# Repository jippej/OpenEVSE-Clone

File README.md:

# OpenEVSE-Clone

This is an hardware design which is based on OpenEVSE, compatible with the OpenEVSE firmware, and suited to my needs.
Key changes in respect to the original OpenEVSE boards (version 5.5):
- Removed DC relais control (I use a AC controlled relais)
- GFCI detection removed (I use an external ELCB)
- Removed AC/DC converter (I use an external DIN rail mounted 12VDC supply)
- form factor adjusted to be fitted in a standard DIN rail housing
- Added H-Bridge driver for "cable lock" mechanism
- Added mounting for ESP32 Gateway

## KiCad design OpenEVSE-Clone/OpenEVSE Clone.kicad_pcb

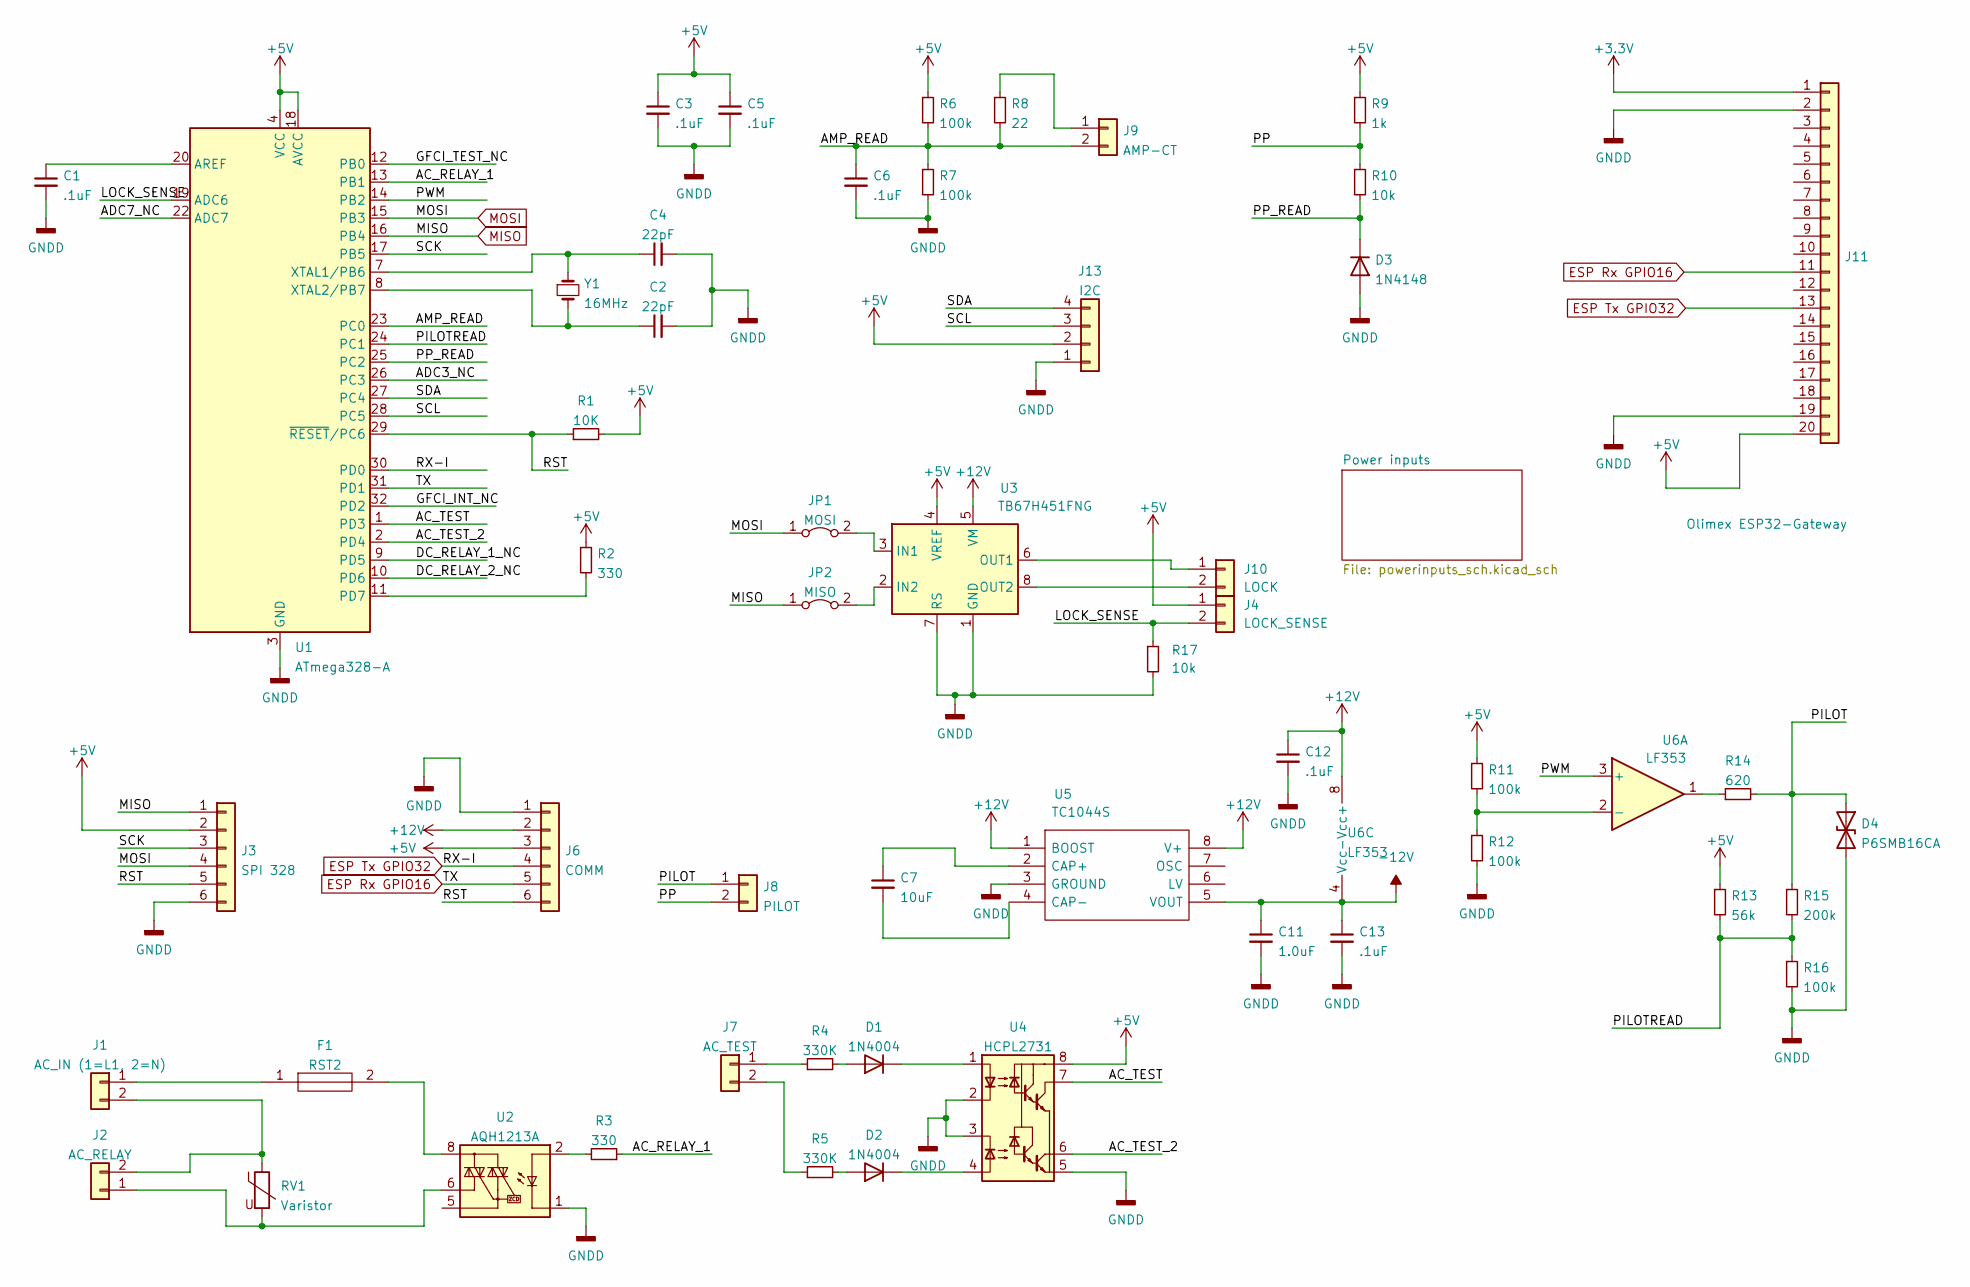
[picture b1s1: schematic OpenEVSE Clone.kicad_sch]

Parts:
C1, C3, C5, C6, C12, C13: .1uF; C_0805_2012Metric_Pad1.18x1.45mm_HandSolder
C2, C4: 22pF; C_0805_2012Metric_Pad1.18x1.45mm_HandSolder
C7: 10uF; C_0805_2012Metric_Pad1.18x1.45mm_HandSolder
C11: 1.0uF; C_0805_2012Metric_Pad1.18x1.45mm_HandSolder
D1, D2: 1N4004; D_SMA
D3: 1N4148; D_SOD-123
D4: P6SMB16CA; D_SMB
F1: RST2; RST2AMMO; Manufacturer_Part_Number RST 2 AMMO; Mouser Part Number 530-RST2AMMO
J1: AC_IN (1=L1, 2=N); TerminalBlock_Phoenix_MKDS-3-2-5.08_1x02_P5.08mm_Horizontal
J2: AC_RELAY; TerminalBlock_Phoenix_MKDS-3-2-5.08_1x02_P5.08mm_Horizontal
J3: SPI 328; PinHeader_2x03_P2.54mm_Vertical
J4: LOCK_SENSE; TerminalBlock_Phoenix_MKDS-3-2-5.08_1x02_P5.08mm_Horizontal
J6: COMM; PinHeader_2x03_P2.54mm_Vertical
J7: AC_TEST; TerminalBlock_Phoenix_MKDS-3-2-5.08_1x02_P5.08mm_Horizontal
J8: PILOT; TerminalBlock_Phoenix_MKDS-3-2-5.08_1x02_P5.08mm_Horizontal
J9: AMP-CT; TerminalBlock_Phoenix_MKDS-3-2-5.08_1x02_P5.08mm_Horizontal
J10: LOCK; TerminalBlock_Phoenix_MKDS-3-2-5.08_1x02_P5.08mm_Horizontal
J11: Olimex ESP32-Gateway; PinSocket_1x20_P2.54mm_Vertical
J13: I2C; PinHeader_1x04_P2.54mm_Vertical
JP1: MOSI; PinSocket_1x02_P2.54mm_Vertical
JP2: MISO; PinSocket_1x02_P2.54mm_Vertical
R1: 10K; R_0805_2012Metric_Pad1.20x1.40mm_HandSolder
R2, R3: 330; R_0805_2012Metric_Pad1.20x1.40mm_HandSolder
R4, R5: 330K; R_2512_6332Metric
R6, R7, R11, R12, R16: 100k; R_0805_2012Metric_Pad1.20x1.40mm_HandSolder
R8: 22; R_0805_2012Metric_Pad1.20x1.40mm_HandSolder
R9: 1k; R_0805_2012Metric_Pad1.20x1.40mm_HandSolder
R10, R17: 10k; R_0805_2012Metric_Pad1.20x1.40mm_HandSolder
R13: 56k; R_0805_2012Metric_Pad1.20x1.40mm_HandSolder
R14: 620; R_0805_2012Metric_Pad1.20x1.40mm_HandSolder
R15: 200k; R_0805_2012Metric_Pad1.20x1.40mm_HandSolder
RV1: Varistor; RV_Disc_D7mm_W4.5mm_P5mm
U1: ATmega328-A; TQFP-32_7x7mm_P0.8mm
U2: AQH1213A; SSO-7-8_6.4x9.78mm_P2.54mm
U3: TB67H451FNG; HSOP-8-1EP_3.9x4.9mm_P1.27mm_EP2.41x3.1mm_ThermalVias
U4: HCPL2731; SMDIP-8_W9.53mm
U5: TC1044S; SOIC-8_3.9x4.9mm_P1.27mm; Manufacturer_Part_Number LTC1044CN8#PBF; Mouser Part Number 584-LTC1044CN8#PBF
U6: LF353; SOIC-8_3.9x4.9mm_P1.27mm
Y1: 16MHz; Crystal_SMD_2016-4Pin_2.0x1.6mm

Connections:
+3.3V: J11.1
+5V: C3.1, C5.1, J3.2, J4.1, J6.3, J11.20, J13.2, R1.2, R2.1, R6.1, R9.1, R11.1, R13.1, U1.4 (VCC), U1.6 (VCC), U1.18 (AVCC), U3.4 (VREF), U4.8 (VCC); also elsewhere on the board
+12V: C12.1, J6.2, U3.5 (VM), U5.1 (BOOST), U5.8 (V+), U6.8 (Vcc+); also elsewhere on the board
-12V: C11.1, C13.1, U5.5 (VOUT), U6.4 (Vcc-)
/AC_RELAY_1: R3.1, U1.13 (PB1)
/AC_TEST: U1.1 (PD3), U4.7 (VO1)
/AC_TEST_2: U1.2 (PD4), U4.6 (VO2)
/ADC3_NC: U1.26 (PC3)
/ADC7_NC: U1.22 (ADC7)
/AMP_READ: C6.1, J9.2, R6.2, R7.1, R8.2, U1.23 (PC0)
/DC_RELAY_1_NC: U1.9 (PD5)
/DC_RELAY_2_NC: U1.10 (PD6)
/GFCI_INT_NC: U1.32 (PD2)
/GFCI_TEST_NC: U1.12 (PB0)
/LOCK_SENSE: J4.2, R17.1, U1.19 (ADC6)
/PILOT: D4.1 (A1), J8.1, R14.2, R15.1
/PILOTREAD: R13.2, R15.2, R16.1, U1.24 (PC1)
/PP: J8.2, R9.2, R10.1
/PP_READ: D3.1 (K), R10.2, U1.25 (PC2)
/PWM: U1.14 (PB2), U6.3 (+)
/RST: J3.5, J6.6, R1.1, U1.29 (~RESET/PC6)
/SCK: J3.3, U1.17 (PB5)
/SCL: J13.3, U1.28 (PC5)
/SDA: J13.4, U1.27 (PC4)
ESP Rx GPIO16: J6.5, J11.11, U1.31 (PD1)
ESP Tx GPIO32: J6.4, J11.13, U1.30 (PD0)
GNDD: C1.2, C2.2, C3.2, C4.2, C5.2, C6.2, C11.2, C12.2, C13.2, D3.2 (A), D4.2 (A2), J3.6, J6.1, J11.2, J11.19, J13.1, R7.2, R12.2, R16.2, R17.2, U1.3 (GND), U1.5 (GND), U1.21 (GND), U2.1, U2.3, U2.4, U3.1 (GND), U3.7 (RS), U3.9 (GND), U4.2 (C1), U4.3 (C2), U4.5 (GND), U5.3 (GROUND); also elsewhere on the board
MISO: J3.1, JP2.1 (A), U1.16 (PB4)
MOSI: J3.4, JP1.1 (A), U1.15 (PB3)
unnamed: C1.1, U1.20 (AREF)
unnamed: C2.1, U1.8 (XTAL2/PB7), Y1.2
unnamed: C4.1, U1.7 (XTAL1/PB6), Y1.1
unnamed: C7.1, U5.2 (CAP+)
unnamed: C7.2, U5.4 (CAP-)
unnamed: D1.1 (K), U4.1 (A1)
unnamed: D1.2 (A), R4.2
unnamed: D2.1 (K), U4.4 (A2)
unnamed: D2.2 (A), R5.2
unnamed: F1.1, J1.1
unnamed: F1.2, U2.8
unnamed: J1.2, J2.2, RV1.1
unnamed: J2.1, RV1.2, U2.6
unnamed: J7.1, R4.1
unnamed: J7.2, R5.1
unnamed: J9.1, R8.1
unnamed: J10.1, U3.6 (OUT1)
unnamed: J10.2, U3.8 (OUT2)
unnamed: JP1.2 (B), U3.3 (IN1)
unnamed: JP2.2 (B), U3.2 (IN2)
unnamed: R2.2, U1.11 (PD7)
unnamed: R3.2, U2.2
unnamed: R11.2, R12.1, U6.2 (-)
unnamed: R14.1, U6.1

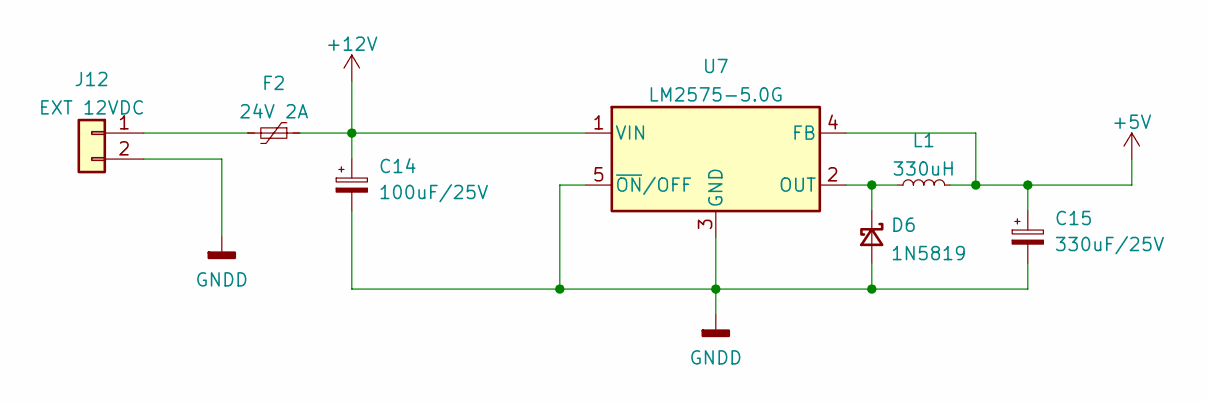
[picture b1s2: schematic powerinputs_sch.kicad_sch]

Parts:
C14: 100uF/25V; CP_Radial_D6.3mm_P2.50mm
C15: 330uF/25V; CP_Radial_D10.0mm_P5.00mm
D6: 1N5819; D_SOD-123
F2: 24V 2A; Fuse_2920_7451Metric_Pad2.10x5.45mm_HandSolder
J12: EXT 12VDC; TerminalBlock_Phoenix_MKDS-3-2-5.08_1x02_P5.08mm_Horizontal
L1: 330uH; L_Radial_D8.7mm_P5.00mm_Fastron_07HCP
U7: LM2575-5.0G; TO-263-5_TabPin3

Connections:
+5V: C15.1, L1.2, U7.4 (FB); also elsewhere on the board
+12V: C14.1, F2.1, U7.1 (VIN); also elsewhere on the board
GNDD: C14.2, C15.2, D6.2 (A), J12.2, U7.3 (GND), U7.5 (~ON/OFF); also elsewhere on the board
unnamed: D6.1 (K), L1.1, U7.2 (OUT)
unnamed: F2.2, J12.1

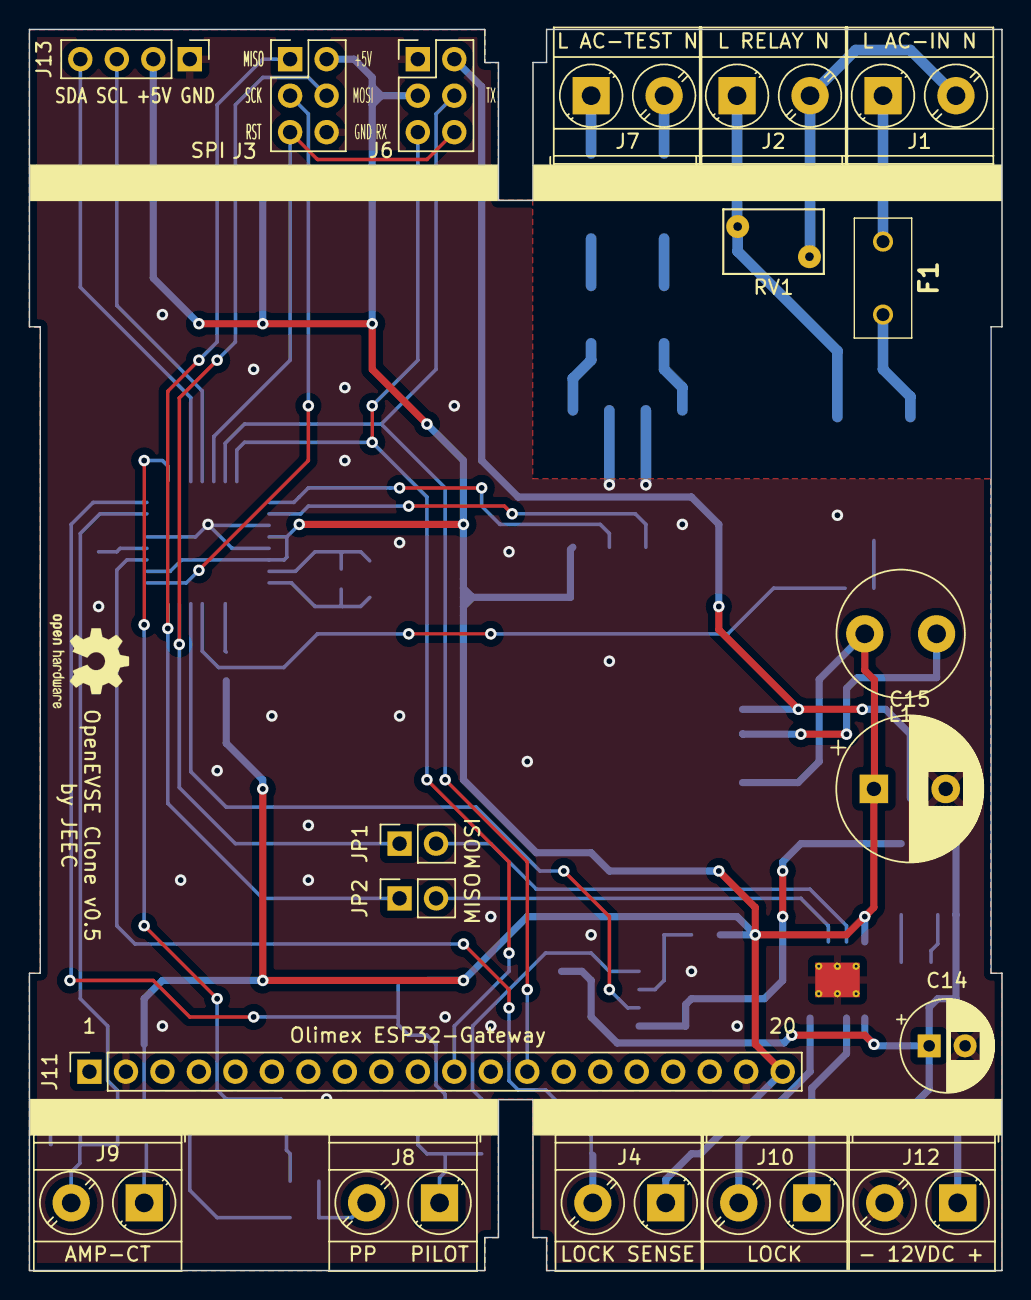
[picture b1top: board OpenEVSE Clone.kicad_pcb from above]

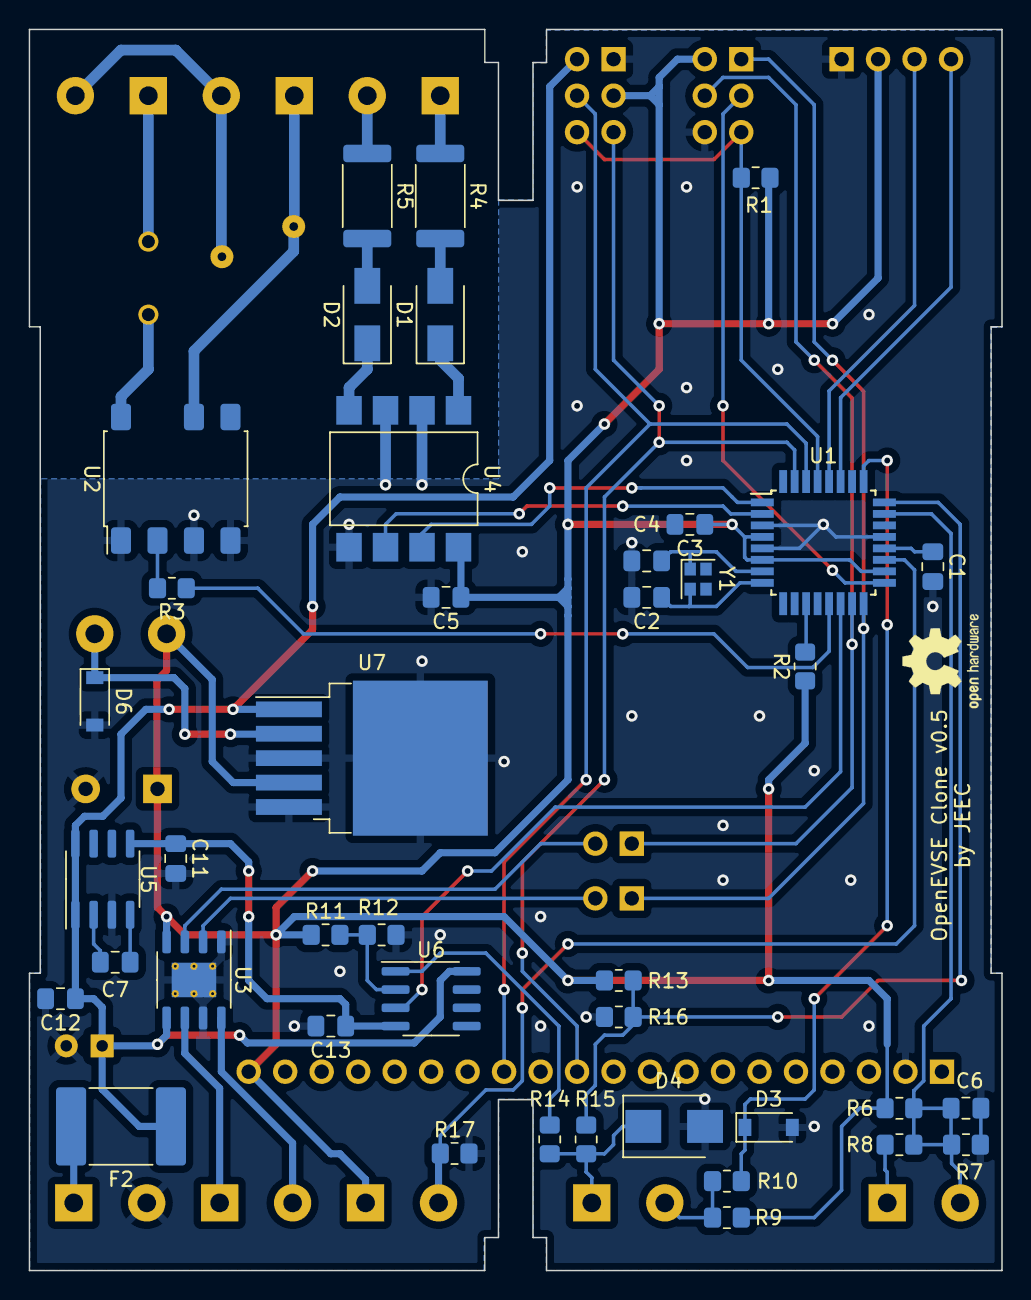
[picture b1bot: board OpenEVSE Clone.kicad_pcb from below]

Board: 2 copper layers, 67.7 x 86.4 mm, 60 parts (41 on the bottom side), 48 nets.

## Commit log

2023-04-26 Schematics and PCB layout added
2024-02-28 Changed folder name
